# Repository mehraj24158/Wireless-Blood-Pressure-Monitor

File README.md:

# Wireless-Blood-Pressure-Monitor
A wireless blood pressure monitor with completed hardware design. Software development is still in progress for the bluetooth enabled microcontroller. A PCB design software(KiCad, Eagle, Etc.) is required to open the files. For accessibility, I have stored images of the schematic and PCB layout in a seperate images folder.

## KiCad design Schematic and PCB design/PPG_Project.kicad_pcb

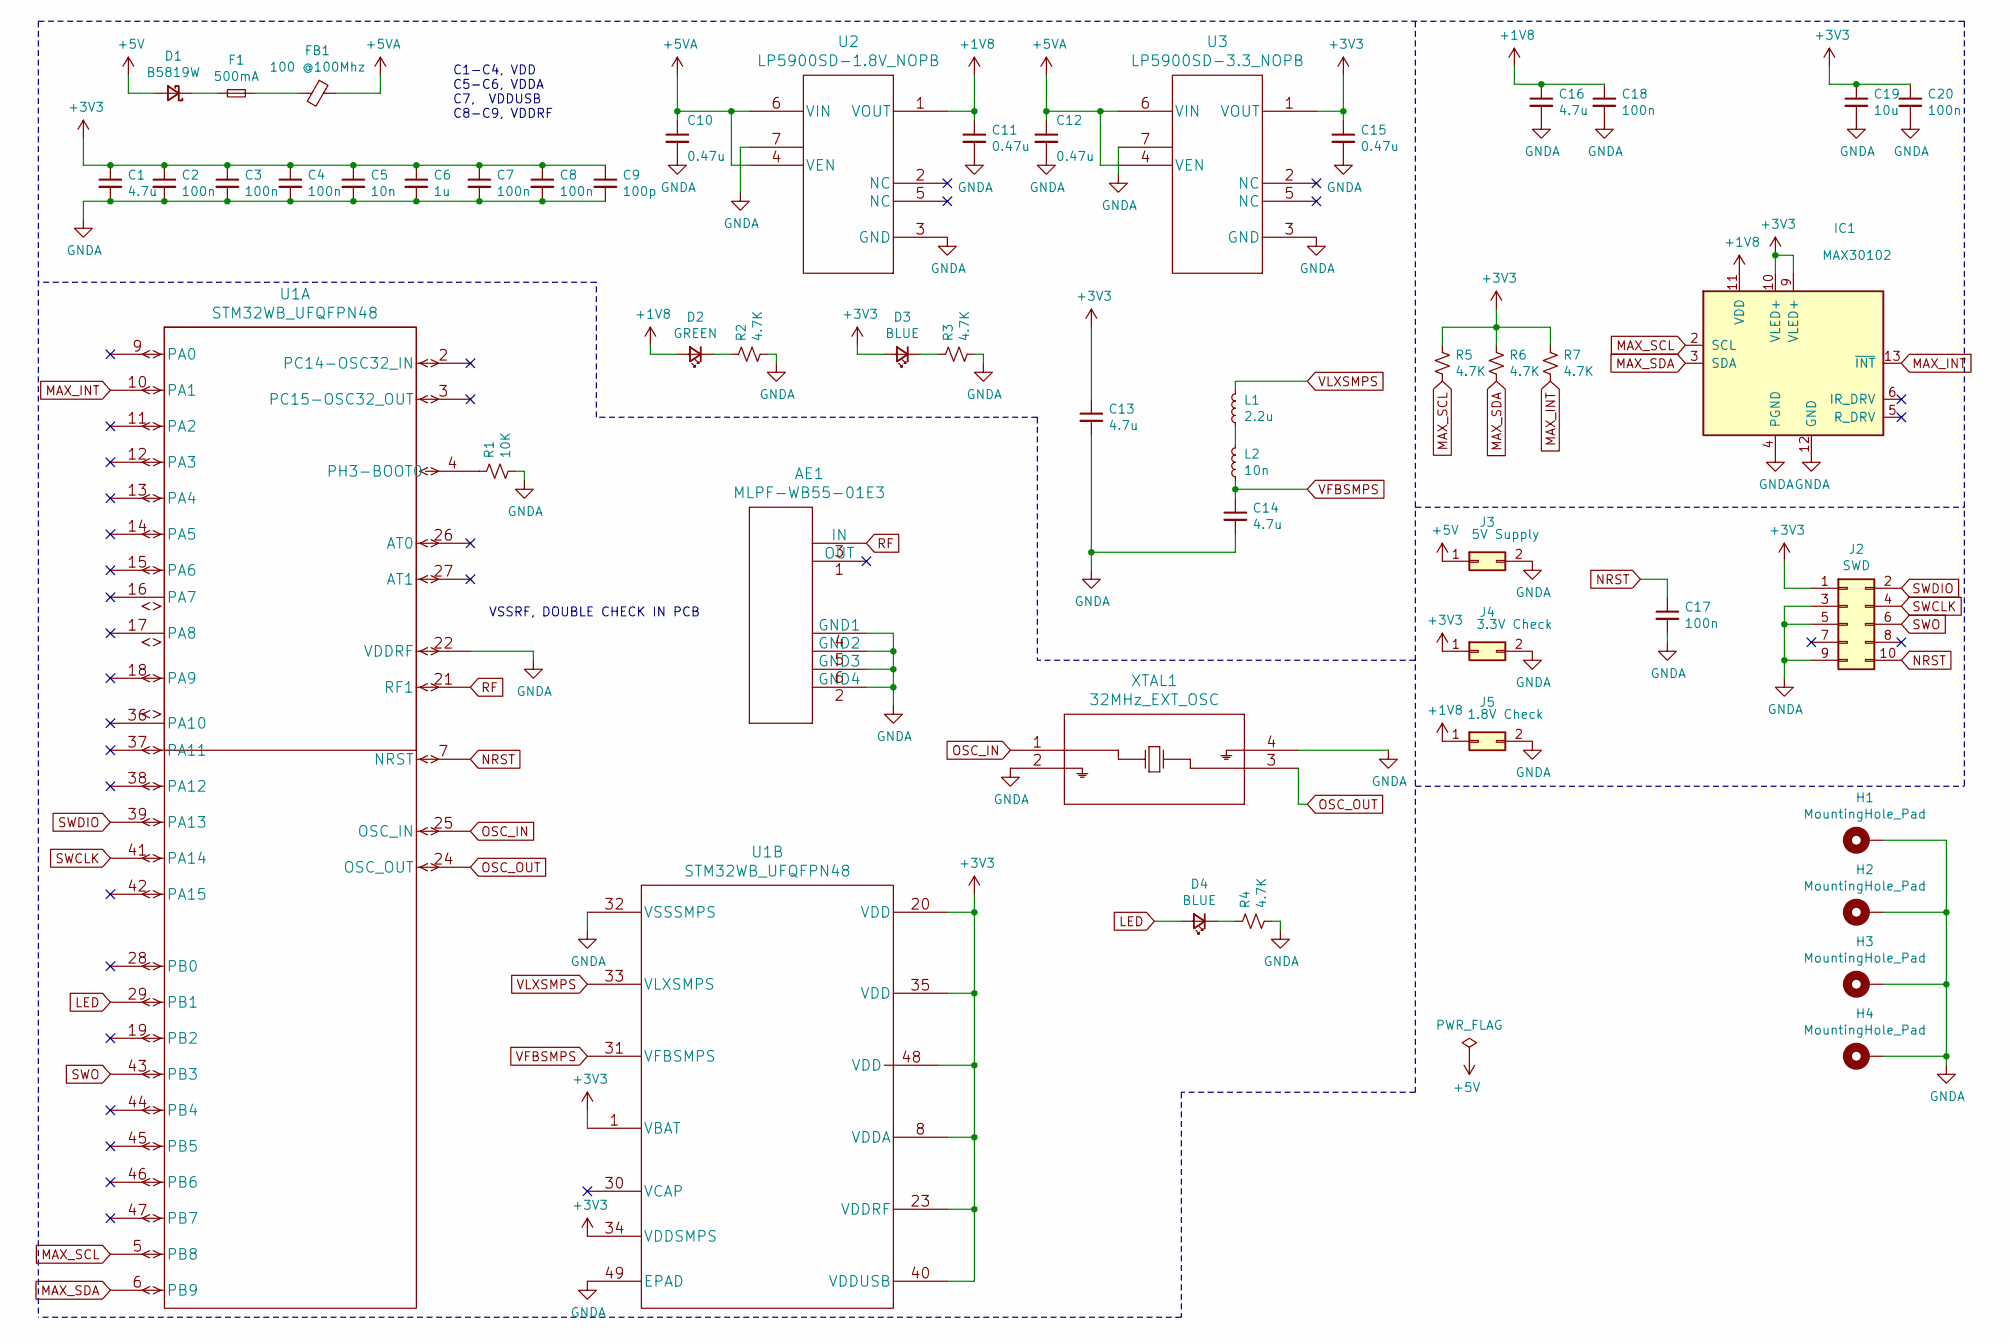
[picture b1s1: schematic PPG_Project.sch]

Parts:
AE1: MLPF-WB55-01E3
C1, C13, C14, C16: 4.7u; C_0603_1608Metric_Pad1.05x0.95mm_HandSolder
C2, C3, C4, C7, C8, C17, C18, C20: 100n; C_0603_1608Metric_Pad1.05x0.95mm_HandSolder
C5: 10n; C_0603_1608Metric_Pad1.05x0.95mm_HandSolder
C6: 1u; C_0603_1608Metric_Pad1.05x0.95mm_HandSolder
C9: 100p; C_0603_1608Metric_Pad1.05x0.95mm_HandSolder
C10, C11, C12, C15: 0.47u; C_0603_1608Metric_Pad1.05x0.95mm_HandSolder
C19: 10u; C_0603_1608Metric_Pad1.05x0.95mm_HandSolder
D1: B5819W; D_0805_2012Metric_Pad1.15x1.40mm_HandSolder
D2: GREEN; LED_0603_1608Metric_Pad1.05x0.95mm_HandSolder
D3, D4: BLUE; LED_0603_1608Metric_Pad1.05x0.95mm_HandSolder
F1: 500mA; Fuse_0805_2012Metric_Pad1.15x1.40mm_HandSolder
FB1: 100 @100Mhz; R_0805_2012Metric_Pad1.15x1.40mm_HandSolder
H1, H2, H3, H4: MountingHole_Pad; MountingHole_4.3mm_M4_Pad_Via
IC1: MAX30102; Maxim_OLGA-14_3.3x5.6mm_P0.8mm
J2: SWD; PinHeader_2x05_P2.54mm_Vertical_SMD
J3: 5V Supply; PinHeader_2x01_P2.54mm_Vertical_SMD
J4: 3.3V Check; PinHeader_2x01_P2.54mm_Vertical_SMD
J5: 1.8V Check; PinHeader_2x01_P2.54mm_Vertical_SMD
L1: 2.2u; L_0603_1608Metric_Pad1.05x0.95mm_HandSolder
L2: 10n; L_0603_1608Metric_Pad1.05x0.95mm_HandSolder
R1: 10K; C_0603_1608Metric_Pad1.05x0.95mm_HandSolder
R2, R3, R4, R5, R6, R7: 4.7K; C_0603_1608Metric_Pad1.05x0.95mm_HandSolder
U1: STM32WB_UFQFPN48
U2: LP5900SD-1.8V_NOPB; LP5900SD-1.5&slash_NOPB
U3: LP5900SD-3.3_NOPB; LP5900SD-1.5&slash_NOPB
XTAL1: 32MHz_EXT_OSC; NX2016SA-40M-STD-CZS-3

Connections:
+1V8: C11.1, C16.1, C18.1, D2.2 (A), IC1.11 (VDD), J5.1, U2.1 (VOUT)
+3V3: C1.1, C2.1, C3.1, C4.1, C5.1, C6.1, C7.1, C8.1, C9.1, C13.1, C15.1, C19.1, C20.1, D3.2 (A), IC1.9 (VLED+), IC1.10 (VLED+), J2.1, J4.1, R5.1, R6.1, R7.1, U1.1 (VBAT), U1.8 (VDDA), U1.20 (VDD), U1.23 (VDDRF), U1.34 (VDDSMPS), U1.35 (VDD), U1.40 (VDDUSB), U1.48 (VDD), U3.1 (VOUT)
+5V: D1.2 (A), J3.1
+5VA: C10.1, C12.1, FB1.1, U2.4 (VEN), U2.6 (VIN), U3.4 (VEN), U3.6 (VIN)
GNDA: AE1.2 (GND4), AE1.4 (GND1), AE1.5 (GND2), AE1.6 (GND3), C1.2, C2.2, C3.2, C4.2, C5.2, C6.2, C7.2, C8.2, C9.2, C10.2, C11.2, C12.2, C13.2, C14.2, C15.2, C16.2, C17.2, C18.2, C19.2, C20.2, H1.1, H2.1, H3.1, H4.1, IC1.4 (PGND), IC1.12 (GND), J2.3, J2.5, J2.9, J3.2, J4.2, J5.2, R1.2, R2.2, R3.2, R4.2, U1.22 (VDDRF), U1.32 (VSSSMPS), U1.49 (EPAD), U2.3 (GND), U2.7, U3.3 (GND), U3.7, XTAL1.2, XTAL1.4
LED: D4.2 (A), U1.29 (PB1)
MAX_INT: IC1.13 (~INT), R7.2, U1.10 (PA1)
MAX_SCL: IC1.2 (SCL), R5.2, U1.5 (PB8)
MAX_SDA: IC1.3 (SDA), R6.2, U1.6 (PB9)
NRST: C17.1, J2.10, U1.7 (NRST)
unnamed: D1.1 (K), F1.1
unnamed: D2.1 (K), R2.1
unnamed: D3.1 (K), R3.1
unnamed: D4.1 (K), R4.1
unnamed: F1.2, FB1.2
unnamed: L1.1, L2.2
unnamed: R1.1, U1.4 (PH3-BOOT0)
OSC_IN: U1.25 (OSC_IN), XTAL1.1
OSC_OUT: U1.24 (OSC_OUT), XTAL1.3
RF: AE1.3 (IN), U1.21 (RF1)
SWCLK: J2.4, U1.41 (PA14)
SWDIO: J2.2, U1.39 (PA13)
SWO: J2.6, U1.43 (PB3)
VFBSMPS: C14.1, L2.1, U1.31 (VFBSMPS)
VLXSMPS: L1.2, U1.33 (VLXSMPS)

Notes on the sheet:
VSSRF, DOUBLE CHECK IN PCB
C1-C4, VDD C5-C6, VDDA C7, VDDUSB C8-C9, VDDRF

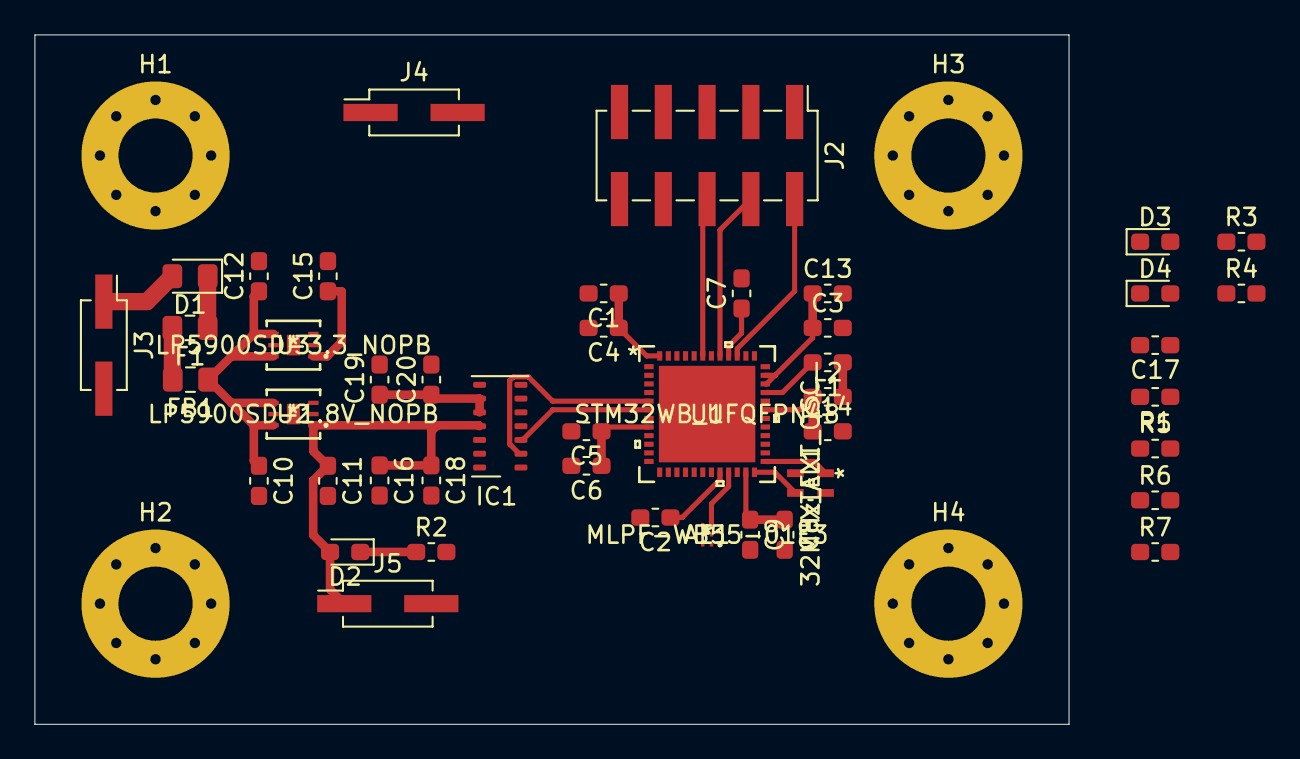
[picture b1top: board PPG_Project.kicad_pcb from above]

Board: 4 copper layers, 60.0 x 40.0 mm, 49 parts (0 on the bottom side), 25 nets.

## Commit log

2020-07-17 Add files via upload
    Added Kicad design
2020-07-17 Add files via upload
    Added Kicad Libraries

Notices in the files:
parts and their libraries:
Copyright 2016 Accelerated Designs. All rights reserved.
